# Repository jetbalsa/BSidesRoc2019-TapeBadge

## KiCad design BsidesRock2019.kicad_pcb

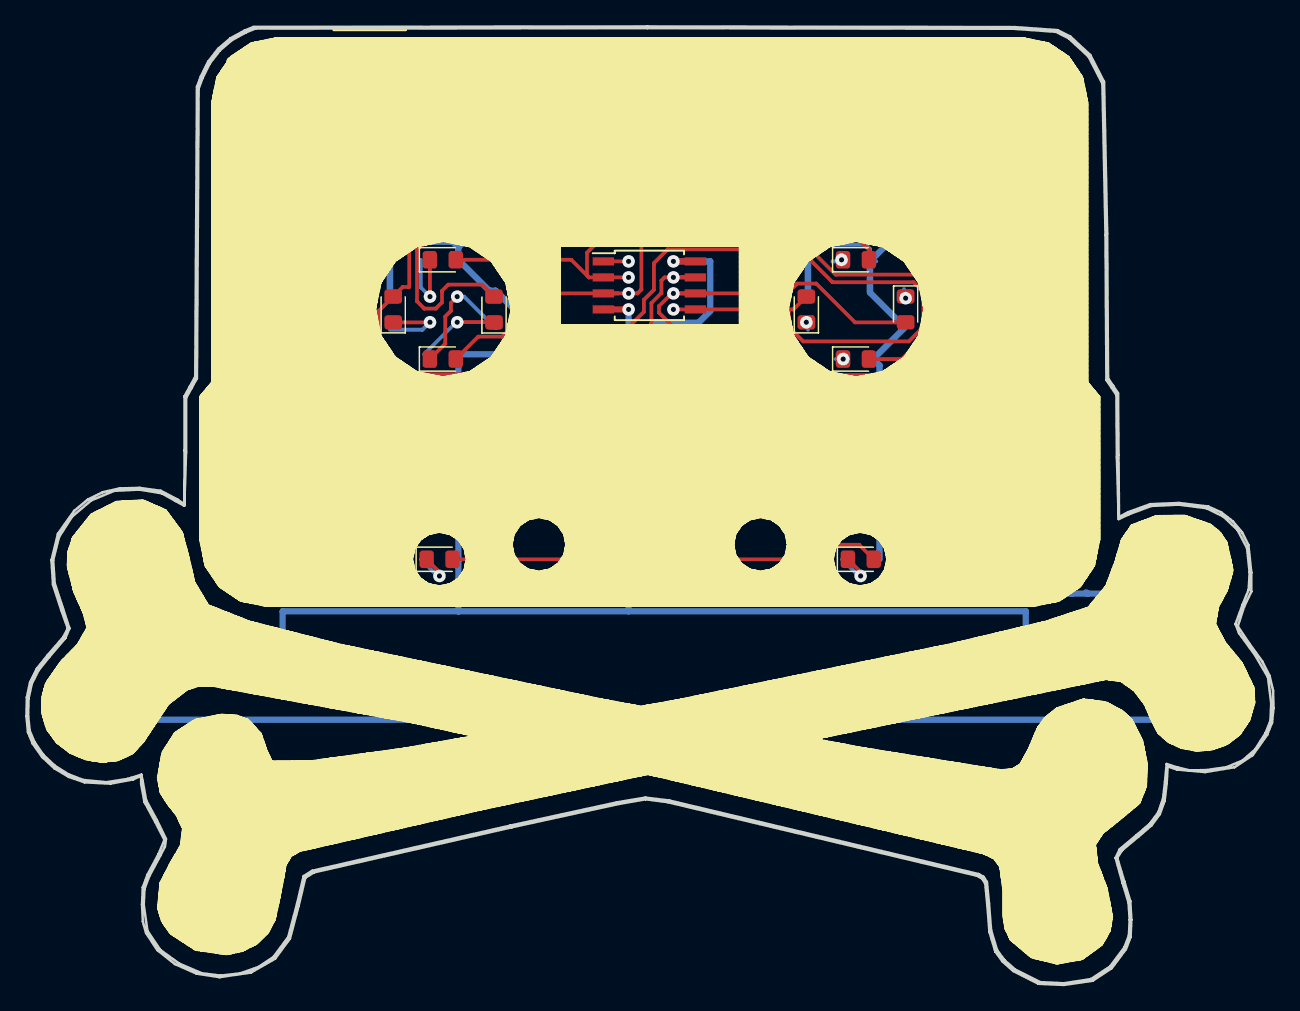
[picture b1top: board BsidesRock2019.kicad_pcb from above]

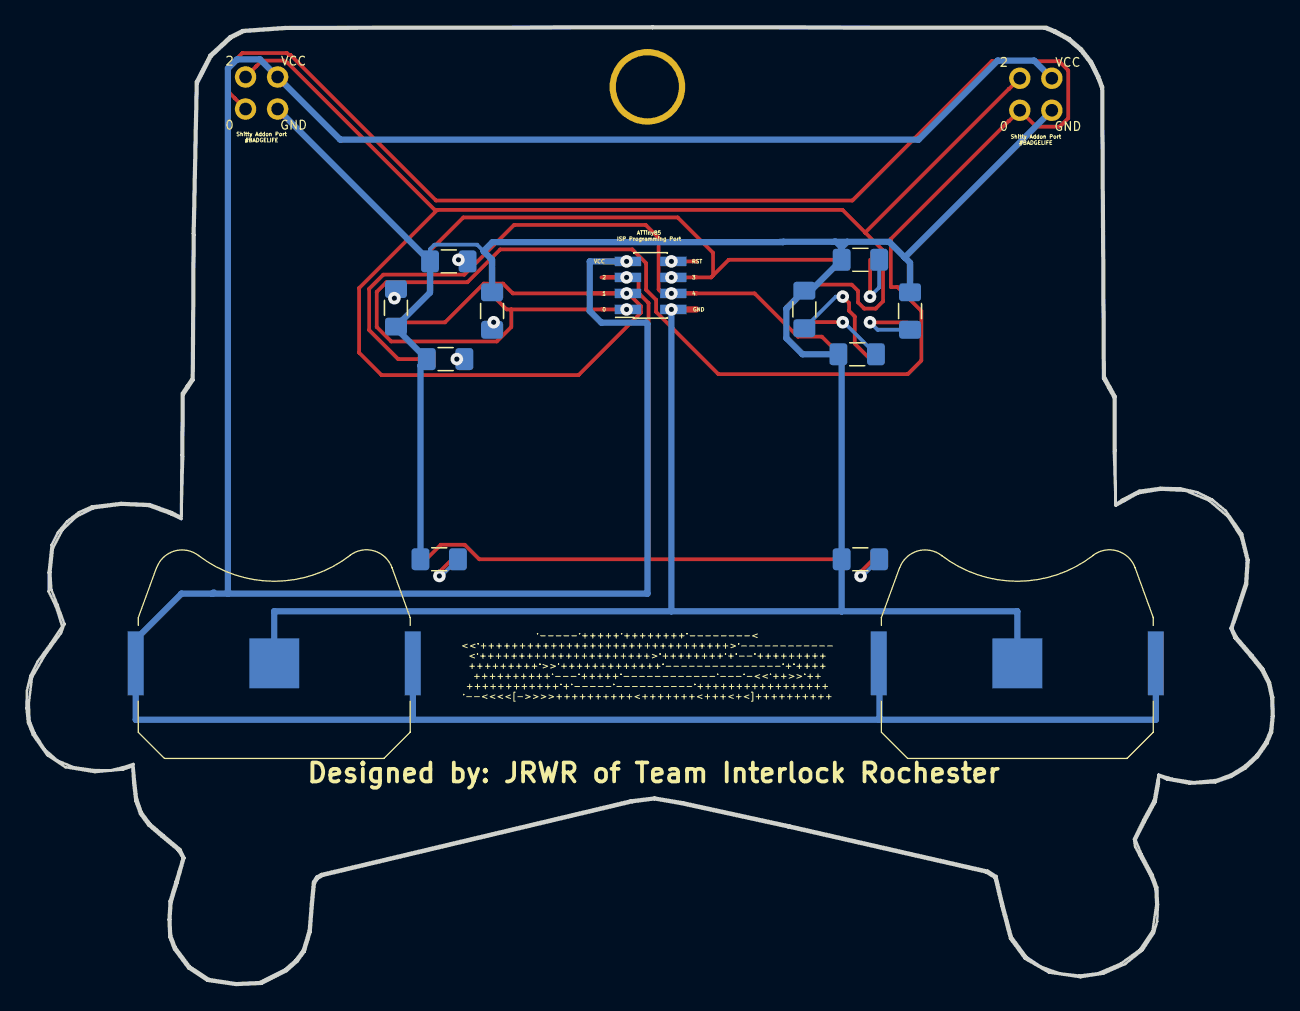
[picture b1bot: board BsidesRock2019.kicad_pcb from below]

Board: 2 copper layers, 98.9 x 76.0 mm, 27 parts (13 on the bottom side), 17 nets.

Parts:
BLANKHOLE: TestPoint_Plated_Hole_D5.0mm
BT-2032-1, BT-2032-2: Battery_Cell; BatteryHolder_Keystone_3034_1x20mm
D1, D2, D3, D4, D5, D6, D7, D8, D9, D10: LED; LED_0805_2012Metric_Pad1.15x1.40mm_HandSolder
J2, J2#2: #badgelife; Badgelife-Shitty-2x2
R56-Ohm1, R56-Ohm2, R56-Ohm3, R56-Ohm4, R56-Ohm5, R56-Ohm6, R56-Ohm7, R56-Ohm8, R56-Ohm9, R56-Ohm10: R_Small; R_1206_3216Metric_Pad1.42x1.75mm_HandSolder
SMDPROGCONN: PinSocket_2x04_P1.27mm_Vertical_SMD
U1: ATtiny85V-10SU; SOIJ-8_5.3x5.3mm_P1.27mm

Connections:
unnamed: BT-2032-1.1, BT-2032-2.1, J2.1, J2#2.1, U1.8
unnamed: BT-2032-1.2, BT-2032-2.2, J2.2, J2#2.2, R56-Ohm1.2, R56-Ohm2.2, R56-Ohm3.2, R56-Ohm4.2, R56-Ohm5.2, R56-Ohm6.2, R56-Ohm7.2, R56-Ohm8.2, R56-Ohm9.2, R56-Ohm10.2, U1.4
unnamed: D1.1, R56-Ohm1.1
unnamed: D1.2, D6.2, J2.3, J2#2.3, U1.5
unnamed: D2.1, R56-Ohm4.1
unnamed: D2.2, D9.2, U1.7
unnamed: D3.1, R56-Ohm3.1
unnamed: D3.2, D7.2, U1.2
unnamed: D4.1, R56-Ohm2.1
unnamed: D4.2, D8.2, U1.3
unnamed: D5.1, R56-Ohm5.1
unnamed: D6.1, R56-Ohm7.1
unnamed: D7.1, R56-Ohm8.1
unnamed: D8.1, R56-Ohm9.1
unnamed: D9.1, R56-Ohm6.1
unnamed: D10.1, R56-Ohm10.1
unnamed: D5.2, D10.2, J2.4, J2#2.4, U1.6

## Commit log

2019-07-13 FINAL RELEASE
